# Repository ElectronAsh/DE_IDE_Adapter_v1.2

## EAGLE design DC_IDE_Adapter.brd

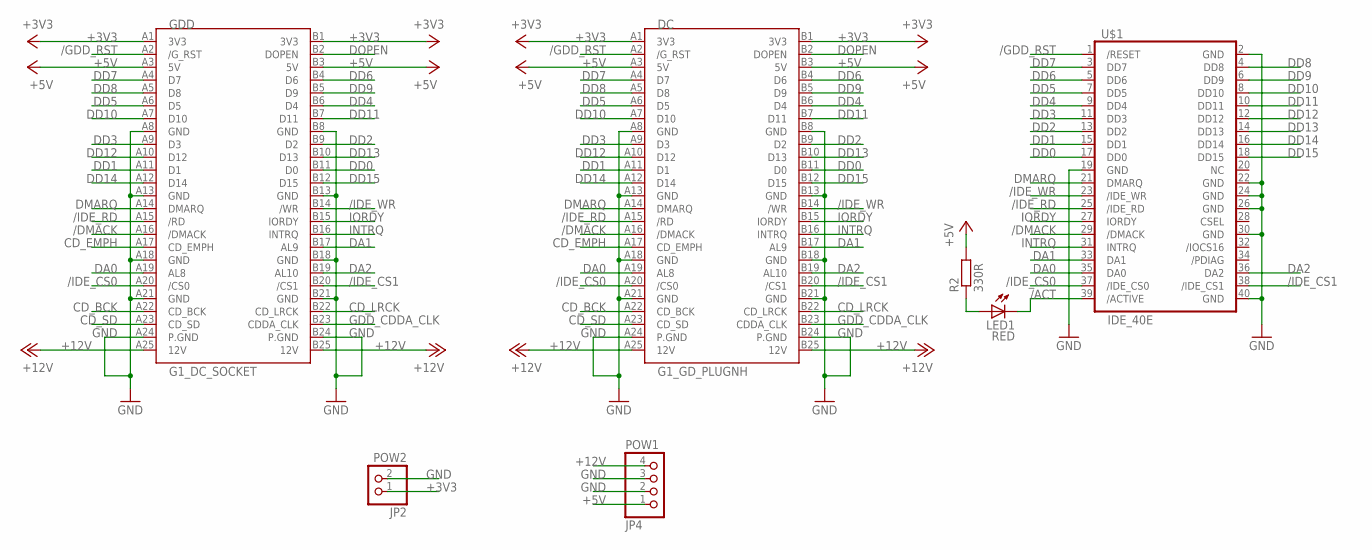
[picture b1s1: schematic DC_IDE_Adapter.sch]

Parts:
DC: G1_GD_PLUGNH; 52584-0579-NOHOLES
GDD: G1_DC_SOCKET; 53408-0579
JP2: POW2; 1X02/90
JP4: POW1; 1X04/90
LED1: RED; LED3MM
R2: 330R; R0603
U$1: IDE_40E; IDE_40_EDGE

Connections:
+3V3: DC.A1 (3V3), DC.B1 (3V3), GDD.A1 (3V3), GDD.B1 (3V3), JP2.1
+5V: DC.A3 (5V), DC.B3 (5V), GDD.A3 (5V), GDD.B3 (5V), JP4.1, R2.2
+12V: DC.A25 (12V), DC.B25 (12V), GDD.A25 (12V), GDD.B25 (12V), JP4.4
/ACT: LED1.K (C), U$1.39 (/ACTIVE)
/DMACK: DC.A16 (/DMACK), GDD.A16 (/DMACK), U$1.29 (/DMACK)
/GDD_RST: DC.A2 (/G_RST), GDD.A2 (/G_RST), U$1.1 (/RESET)
/IDE_CS0: DC.A20 (/CS0), GDD.A20 (/CS0), U$1.37 (/IDE_CS0)
/IDE_CS1: DC.B20 (/CS1), GDD.B20 (/CS1), U$1.38 (/IDE_CS1)
/IDE_RD: DC.A15 (/RD), GDD.A15 (/RD), U$1.25 (/IDE_RD)
/IDE_WR: DC.B14 (/WR), GDD.B14 (/WR), U$1.23 (/IDE_WR)
CD_BCK: DC.A22 (CD_BCK), GDD.A22 (CD_BCK)
CD_EMPH: DC.A17 (CD_EMPH), GDD.A17 (CD_EMPH)
CD_LRCK: DC.B22 (CD_LRCK), GDD.B22 (CD_LRCK)
CD_SD: DC.A23 (CD_SD), GDD.A23 (CD_SD)
DA0: DC.A19 (AL8), GDD.A19 (AL8), U$1.35 (DA0)
DA1: DC.B17 (AL9), GDD.B17 (AL9), U$1.33 (DA1)
DA2: DC.B19 (AL10), GDD.B19 (AL10), U$1.36 (DA2)
DD0: DC.B11 (D0), GDD.B11 (D0), U$1.17 (DD0)
DD1: DC.A11 (D1), GDD.A11 (D1), U$1.15 (DD1)
DD2: DC.B9 (D2), GDD.B9 (D2), U$1.13 (DD2)
DD3: DC.A9 (D3), GDD.A9 (D3), U$1.11 (DD3)
DD4: DC.B6 (D4), GDD.B6 (D4), U$1.9 (DD4)
DD5: DC.A6 (D5), GDD.A6 (D5), U$1.7 (DD5)
DD6: DC.B4 (D6), GDD.B4 (D6), U$1.5 (DD6)
DD7: DC.A4 (D7), GDD.A4 (D7), U$1.3 (DD7)
DD8: DC.A5 (D8), GDD.A5 (D8), U$1.4 (DD8)
DD9: DC.B5 (D9), GDD.B5 (D9), U$1.6 (DD9)
DD10: DC.A7 (D10), GDD.A7 (D10), U$1.8 (DD10)
DD11: DC.B7 (D11), GDD.B7 (D11), U$1.10 (DD11)
DD12: DC.A10 (D12), GDD.A10 (D12), U$1.12 (DD12)
DD13: DC.B10 (D13), GDD.B10 (D13), U$1.14 (DD13)
DD14: DC.A12 (D14), GDD.A12 (D14), U$1.16 (DD14)
DD15: DC.B12 (D15), GDD.B12 (D15), U$1.18 (DD15)
DMARQ: DC.A14 (DMARQ), GDD.A14 (DMARQ), U$1.21 (DMARQ)
DOPEN: DC.B2 (DOPEN), GDD.B2 (DOPEN)
GDD_CDDA_CLK: DC.B23 (CDDA_CLK), GDD.B23 (CDDA_CLK)
GND: DC.A8 (GND), DC.A13 (GND), DC.A18 (GND), DC.A21 (GND), DC.A24 (P.GND), DC.B8 (GND), DC.B13 (GND), DC.B18 (GND), DC.B21 (GND), DC.B24 (P.GND), GDD.A8 (GND), GDD.A13 (GND), GDD.A18 (GND), GDD.A21 (GND), GDD.A24 (P.GND), GDD.B8 (GND), GDD.B13 (GND), GDD.B18 (GND), GDD.B21 (GND), GDD.B24 (P.GND), JP2.2, JP4.2, JP4.3, U$1.2 (GND), U$1.19 (GND), U$1.22 (GND), U$1.24 (GND), U$1.26 (GND), U$1.30 (GND), U$1.40 (GND)
INTRQ: DC.B16 (INTRQ), GDD.B16 (INTRQ), U$1.31 (INTRQ)
IORDY: DC.B15 (IORDY), GDD.B15 (IORDY), U$1.27 (IORDY)
unnamed: LED1.A, R2.1

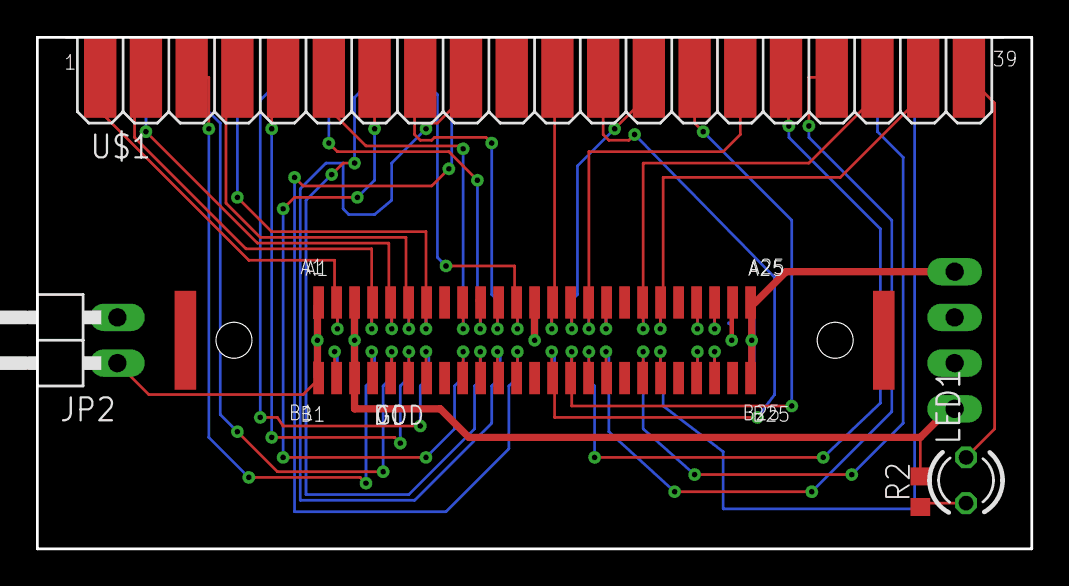
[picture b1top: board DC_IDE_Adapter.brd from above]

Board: 2 copper layers, 55.2 x 28.4 mm, 7 parts (1 on the bottom side), 40 nets.
